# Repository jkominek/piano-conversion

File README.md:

# About

This represents work on hardware/software for converting acoustic
pianos in to full featured MIDI controllers. The idea is to take
untunable pianos, or pianos whose restoration cost would wildly
exceed their value, and make something useful out of them.

See [the FAQ](https://github.com/jkominek/piano-conversion/wiki/FAQ)
to have common / likely questions answered.

Later work may expand that scope.

It was inspired by Evgeni Kumanov (CyberGene)'s "Cybrid" controller:
https://github.com/ekumanov/cybrid/

# Warning!

The hardware designs are unfinished. Some have not been fabricated.
Most have barely been tested, and there is not firmware to run a
completed system.

See the [Status page](https://github.com/jkominek/piano-conversion/wiki/Status) for where things stand.

# A Very Brief Overview

* hardware
  * Where most of the work has taken place. KiCad schematics and board
    layouts for the system.
* cubemx
  * STCubeMX files which correspond to the boards, the idea being that
    if you want to write your own firmware, you can start from here,
    and know that your pin assignments and such are all sane.
* firmware
  * Board firmware, some other stuff
* analyses
  * Data collected, and code/notes for processing it.
* mechanical
  * OpenSCAD files for physical parts which have been useful in
    construction of my prototype.

# More

See [DESIGN.md](https://github.com/jkominek/piano-conversion/blob/master/DESIGN.md) for system design information.

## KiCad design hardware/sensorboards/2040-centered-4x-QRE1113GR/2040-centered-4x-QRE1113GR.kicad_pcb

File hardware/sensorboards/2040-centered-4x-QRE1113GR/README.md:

These are the KiCad files for a sensorboard containing 4 QRE1113GR (surface mount) as in the raytracing below

The image depicts an assembly of sensorboards on thick and thin rails (in dark gray, on the top).
The thick rails will be used for hammer sensors. The hammers will come from down in this picture
and the keys are "inside the screen" toward the left.

The lighter grey "sensor protector" will absorb at least part of the hammer impacts.
All the hammer boards will have those installed, but it is not shown on the board
to the right to show better the board itself. There is a levitating "sensor protector"
on the left, showing the other side with the clearance for the pins.

The board on the left, on the thinner extrusion is identical to the others. The assembly
is slightly different in that the jumper connector will be mounted on
the other side of the board. That, and the thinner extrusion make it a "key sensor" board.
It will need to be flipped upside down for the purpose, and lowered under the keys which
are not shown in this image. All keys will have them (also the keys not damped on a piano:
note off is still needed for MIDI even if it might be ignored by the virtual instrument for
the highest notes of the piano).

Note also that the 3D model of the sensor is taken from a different one and not very accurate
neither quantitatively (i.e. dimensions are incorrect) nor qualitatively (for example it does
not show the little "dips" where the LED and the phototransistors are).
The subdirectory rendering contains more information on the 3D render process

If you want to avoid the hassle of ordering, I am trying to make the whole process easier for you,
but it is not fully working yet. You can track that progress
[here](https://www.pcbway.com/project/shareproject/W341931AX1N3_gerber_54f46d6c.html)

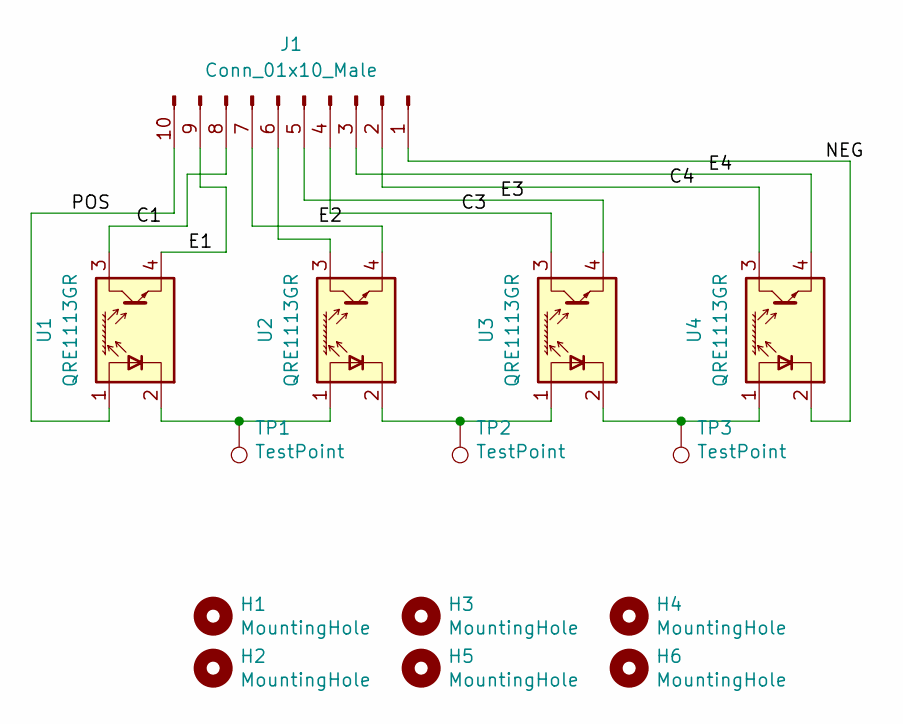
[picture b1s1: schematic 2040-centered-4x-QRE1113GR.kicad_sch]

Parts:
H1, H2, H3, H4, H5, H6: MountingHole; MountingHole_3.2mm_M3
J1: Conn_01x10_Male; PinHeader_1x10_P2.54mm_Vertical
TP1, TP2, TP3: TestPoint; TestPoint_Pad_1.0x1.0mm
U1, U2, U3, U4: QRE1113GR; MPN QRE1113GR

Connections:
/C1: J1.8, U1.3
/C3: J1.4, U3.3
/C4: J1.2, U4.3
/E1: J1.9, U1.4
/E2: J1.7, U2.4
/E3: J1.5, U3.4
/E4: J1.3, U4.4
/NEG: J1.1, U4.2 (K)
/POS: J1.10, U1.1 (A)
unnamed: TP1.1, U1.2 (K), U2.1 (A)
unnamed: TP2.1, U2.2 (K), U3.1 (A)
unnamed: TP3.1, U3.2 (K), U4.1 (A)
unnamed: J1.6, U2.3

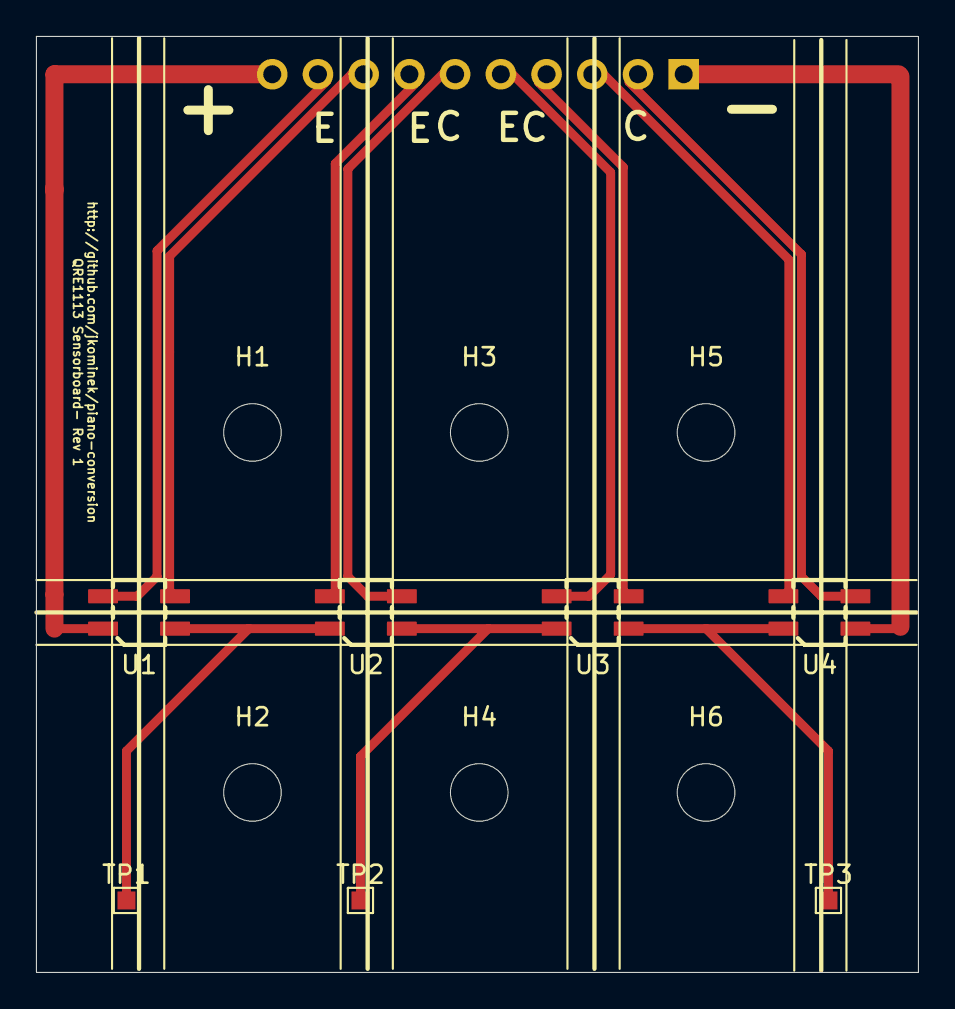
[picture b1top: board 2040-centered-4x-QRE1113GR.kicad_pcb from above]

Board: 2 copper layers, 49.0 x 52.0 mm, 14 parts (1 on the bottom side), 13 nets.

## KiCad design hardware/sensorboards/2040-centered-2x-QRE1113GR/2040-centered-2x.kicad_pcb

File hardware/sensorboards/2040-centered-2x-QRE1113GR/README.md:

These are the KiCad files for a sensoroard containing 2 QRE1113GR (surface mount) as below

The board is asymmetric. I have done that to allow a stable mounting even if the board should be attached to the extrusion via
spacers (which are necessary if one does not fix in other ways the difference between the bass hammers and the rest -- due to the fact
that bass strings cross the other ones and hence are at a different height).

As it should be clear from the picture, this means that 2x sensorboards can **NOT** be used for the whole piano. In fact, a sensor of one side
is too distant from the side of the board to be able to fit another sensorboard nearby and still match the subsequent hammer.
These boards have been designed to be used **only** as end options for the last one or two hammers in each section, where a 4x sensorboard
would not be desirable (for example for space reasons).

At first it seems that this sensorboard can be used only on one side of the section, however if one is flexible with the connector placement
(front or back of the rail) this is not actually a limitation: a 180 degree rotation over the vertical axis will allow to this sensorboard
to be either the first or the last of each section.

Notes:

1. The 3D model of the sensor is taken from a different one and not very accurate (for example it does not show the little "dips" where
   the LED and the phototransistors are)
2. I am not sure I am allowed to include the CAD model of the aluminum extrusion, but you can download it yourself from
   [the HFS4040 page](https://us.misumi-ec.com/vona2/detail/110302684530/) on the Misumi website, and associate it to that "hole" out
   of the board

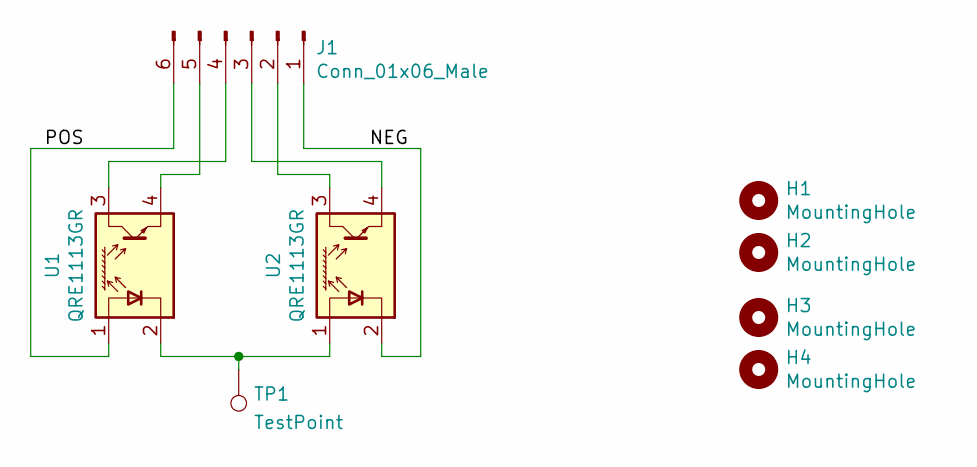
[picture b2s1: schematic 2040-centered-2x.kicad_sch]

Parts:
H1, H2, H3, H4: MountingHole; MountingHole_3.2mm_M3
J1: Conn_01x06_Male; Pin_Header_Angled_1x06_Pitch2.54mm
TP1: TestPoint; TestPoint_Pad_1.0x1.0mm
U1, U2: QRE1113GR

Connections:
/NEG: J1.1, U2.2 (K)
/POS: J1.6, U1.1 (A)
unnamed: TP1.1, U1.2 (K), U2.1 (A)
unnamed: J1.4, U1.3 (C)
unnamed: J1.5, U1.4 (E)
unnamed: J1.2, U2.3 (C)
unnamed: J1.3, U2.4 (E)

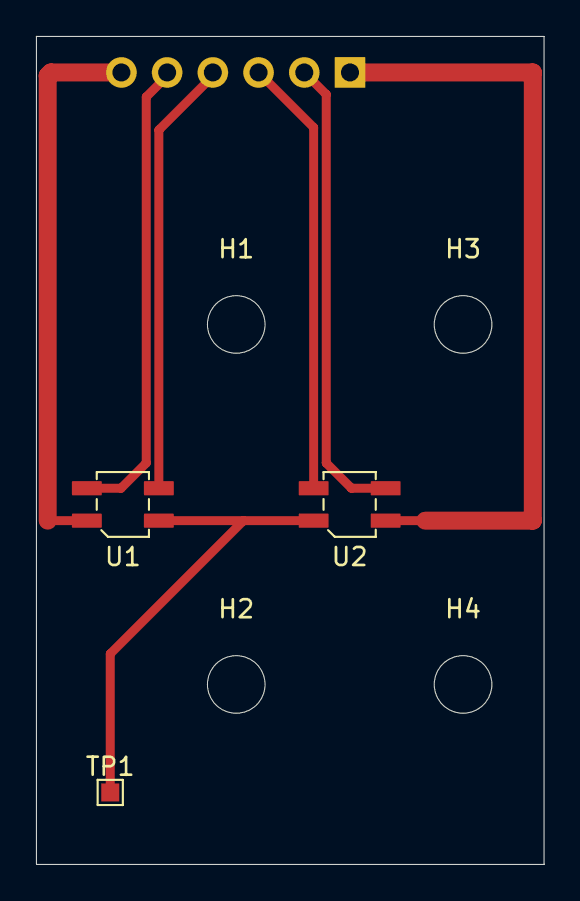
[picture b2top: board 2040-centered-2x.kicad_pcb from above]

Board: 2 copper layers, 28.2 x 46.0 mm, 8 parts (1 on the bottom side), 7 nets.

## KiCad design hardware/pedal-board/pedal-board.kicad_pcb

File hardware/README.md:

# What's in here

* adc-board
  * An STM32H743 reading 22 ADC channels and sending the results over RS485.
* led-power
  * Provides power to 8 strings of 22 CNY70 IR LEDs. Needs +48V. Optional I2C control.
* led-test-bar
  * For development only: little bar that holds a bunch of LEDs for testing the LED power board.
* link-adapter
  * For development only: allows a PC to connect to an ADC or main board.
* main-board
  * 8 ADC boards can plug in, their processed signals are managed
    by another STM32H743 and converted to MIDI in its various forms.
    Intended mainly for USB use, also has ethernet designed in.
    For all of the optional accessories, there are three I2C ports in
    the form of Qwiic connectors, for plugging in MIDI & pedal boards,
    and whatever other craziness you can conjure up.
* midi-board
  * An I2C to MIDI DIN board. Gets the extra UART, optos and DIN
    connectors off the main board so they're not taking up space if
    you don't need them.
* pedal-board
  * 4 1/4" TRS jacks for common MIDI keyboard pedals. STM32G0 for reading
    the signals and making them available to the main board via I2C.
* sensorboard-tester
  * For development/manufacture only, for testing/measuring sensorboards/CNY70s.
* sensorboards
  * Directory with a variety of board configurations for holding CNY70 sensors.

To put a sensor on every hammer and key of an 88 key piano, you would need:

* 176 sensor boards
* 8 ADC boards
* 1 main board
* 1 LED power board

Everything else is optional, but might make your life better.

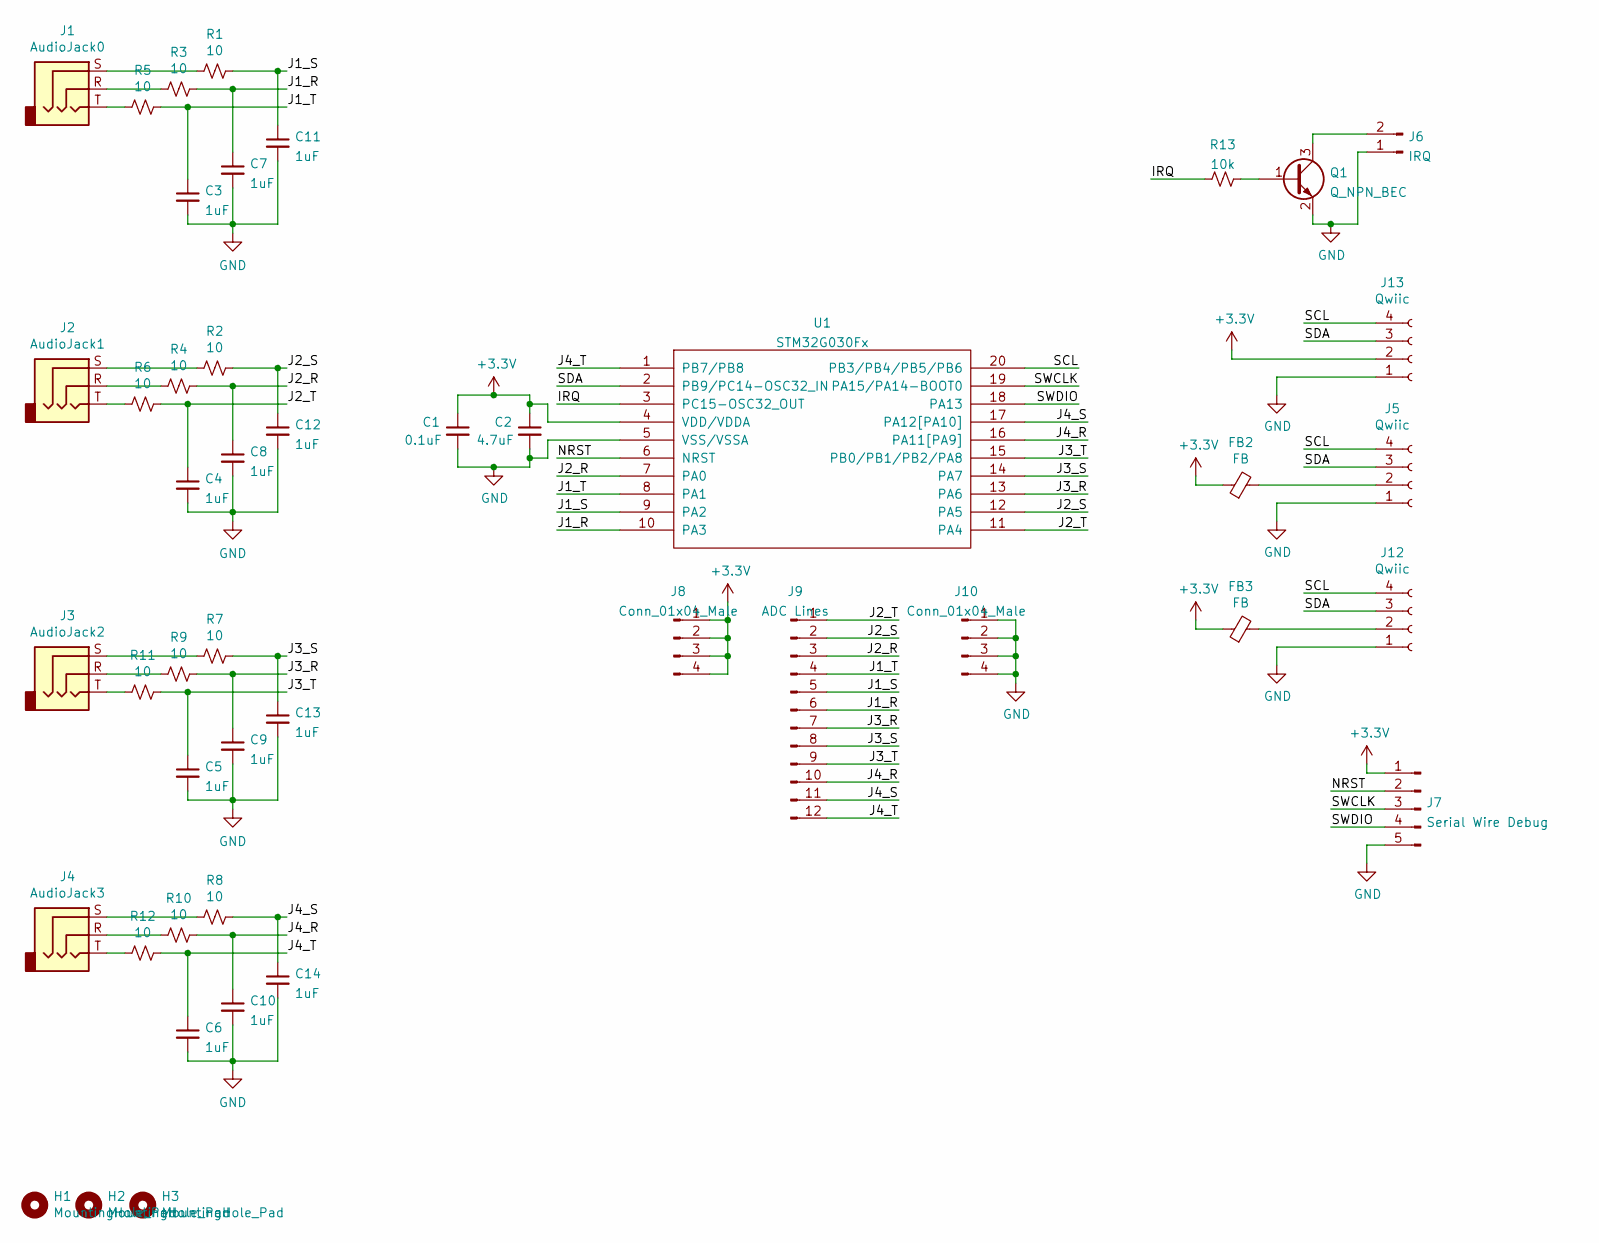
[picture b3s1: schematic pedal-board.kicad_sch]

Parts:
C1: 0.1uF; C_0805_2012Metric_Pad1.18x1.45mm_HandSolder
C2: 4.7uF; C_0805_2012Metric_Pad1.18x1.45mm_HandSolder
C3, C4, C5, C6, C7, C8, C9, C10, C11, C12, C13, C14: 1uF; C_0805_2012Metric_Pad1.18x1.45mm_HandSolder
FB2, FB3: FB; L_0805_2012Metric_Pad1.05x1.20mm_HandSolder
H1, H2, H3: MountingHole_Pad; MountingHole_3.2mm_M3
J1: AudioJack0; SJ-63053A
J2: AudioJack1; SJ-63053A
J3: AudioJack2; SJ-63053A
J4: AudioJack3; SJ-63053A
J5, J12: Qwiic; JST_SH_SM04B-SRSS-TB_04x1.00mm_Angled
J6: IRQ; PinHeader_1x02_P2.54mm_Vertical
J7: Serial Wire Debug; PinHeader_1x05_P2.54mm_Vertical
J8, J10: Conn_01x04_Male; PinHeader_1x04_P2.54mm_Vertical
J9: ADC Lines; PinHeader_1x12_P2.54mm_Vertical
J13: Qwiic; PinHeader_1x04_P2.54mm_Vertical
Q1: Q_NPN_BEC; SOT-23
R1, R2, R3, R4, R5, R6, R7, R8, R9, R10, R11, R12: 10; R_0805_2012Metric_Pad1.20x1.40mm_HandSolder
R13: 10k; R_0805_2012Metric_Pad1.20x1.40mm_HandSolder
U1: STM32G030Fx; TSSOP-20_4.4x6.5mm_P0.65mm

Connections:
+3V3: C1.1, C2.1, FB2.1, FB3.1, J7.1, J8.1, J8.2, J8.3, J8.4, J13.2, U1.4 (VDD/VDDA)
/IRQ: R13.1, U1.3 (PC15-OSC32_OUT)
/J1_R: C7.1, J9.6, R3.1, U1.10 (PA3)
/J1_S: C11.1, J9.5, R1.1, U1.9 (PA2)
/J1_T: C3.1, J9.4, R5.1, U1.8 (PA1)
/J2_R: C8.1, J9.3, R4.1, U1.7 (PA0)
/J2_S: C12.1, J9.2, R2.1, U1.12 (PA5)
/J2_T: C4.1, J9.1, R6.1, U1.11 (PA4)
/J3_R: C9.1, J9.7, R9.1, U1.13 (PA6)
/J3_S: C13.1, J9.8, R7.1, U1.14 (PA7)
/J3_T: C5.1, J9.9, R11.1, U1.15 (PB0/PB1/PB2/PA8)
/J4_R: C10.1, J9.10, R10.1, U1.16 (PA11[PA9])
/J4_S: C14.1, J9.11, R8.1, U1.17 (PA12[PA10])
/J4_T: C6.1, J9.12, R12.1, U1.1 (PB7/PB8)
/NRST: J7.2, U1.6 (NRST)
/SCL: J5.4, J12.4, J13.4, U1.20 (PB3/PB4/PB5/PB6)
/SDA: J5.3, J12.3, J13.3, U1.2 (PB9/PC14-OSC32_IN)
/SWCLK: J7.3, U1.19 (PA15/PA14-BOOT0)
/SWDIO: J7.4, U1.18 (PA13)
GND: C1.2, C2.2, C3.2, C4.2, C5.2, C6.2, C7.2, C8.2, C9.2, C10.2, C11.2, C12.2, C13.2, C14.2, J5.1, J6.1, J7.5, J10.1, J10.2, J10.3, J10.4, J12.1, J13.1, Q1.2 (E), U1.5 (VSS/VSSA)
unnamed: FB2.2, J5.2
unnamed: FB3.2, J12.2
unnamed: J1.R, R3.2
unnamed: J1.S, R1.2
unnamed: J1.T, R5.2
unnamed: J2.R, R4.2
unnamed: J2.S, R2.2
unnamed: J2.T, R6.2
unnamed: J3.R, R9.2
unnamed: J3.S, R7.2
unnamed: J3.T, R11.2
unnamed: J4.R, R10.2
unnamed: J4.S, R8.2
unnamed: J4.T, R12.2
unnamed: J6.2, Q1.3 (C)
unnamed: Q1.1 (B), R13.2

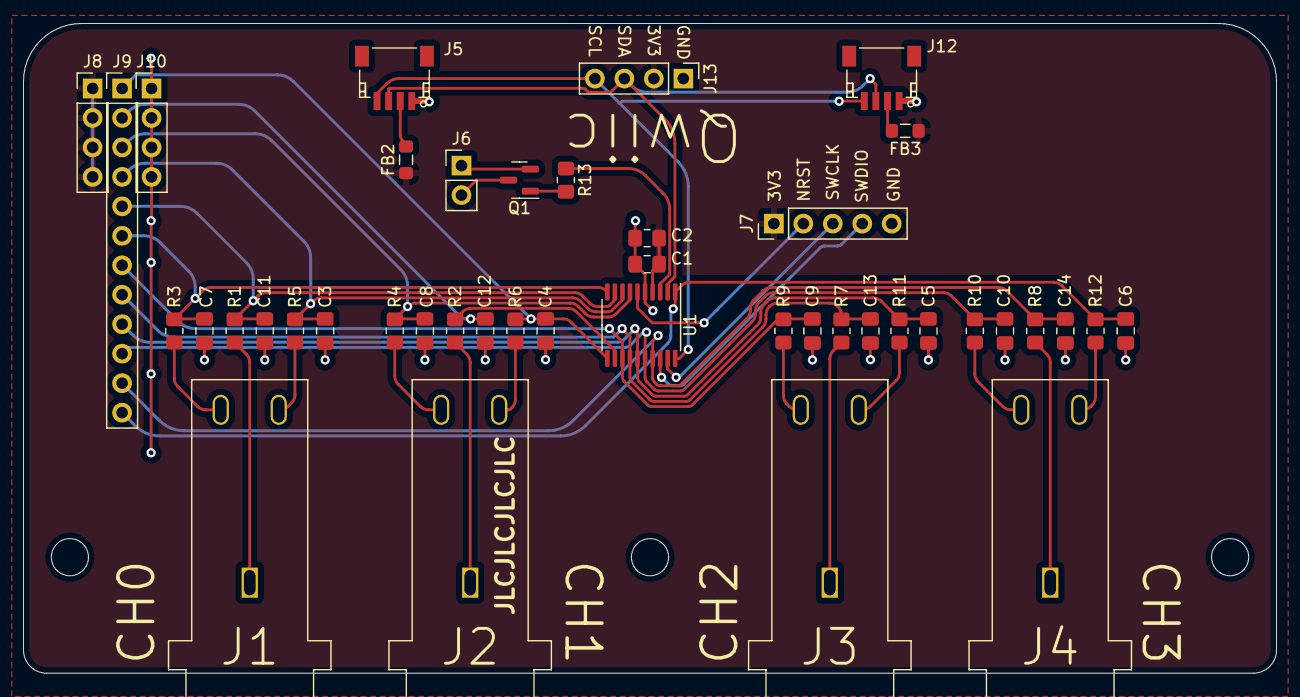
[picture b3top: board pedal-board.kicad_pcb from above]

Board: 2 copper layers, 108.0 x 56.0 mm, 46 parts (0 on the bottom side), 36 nets.

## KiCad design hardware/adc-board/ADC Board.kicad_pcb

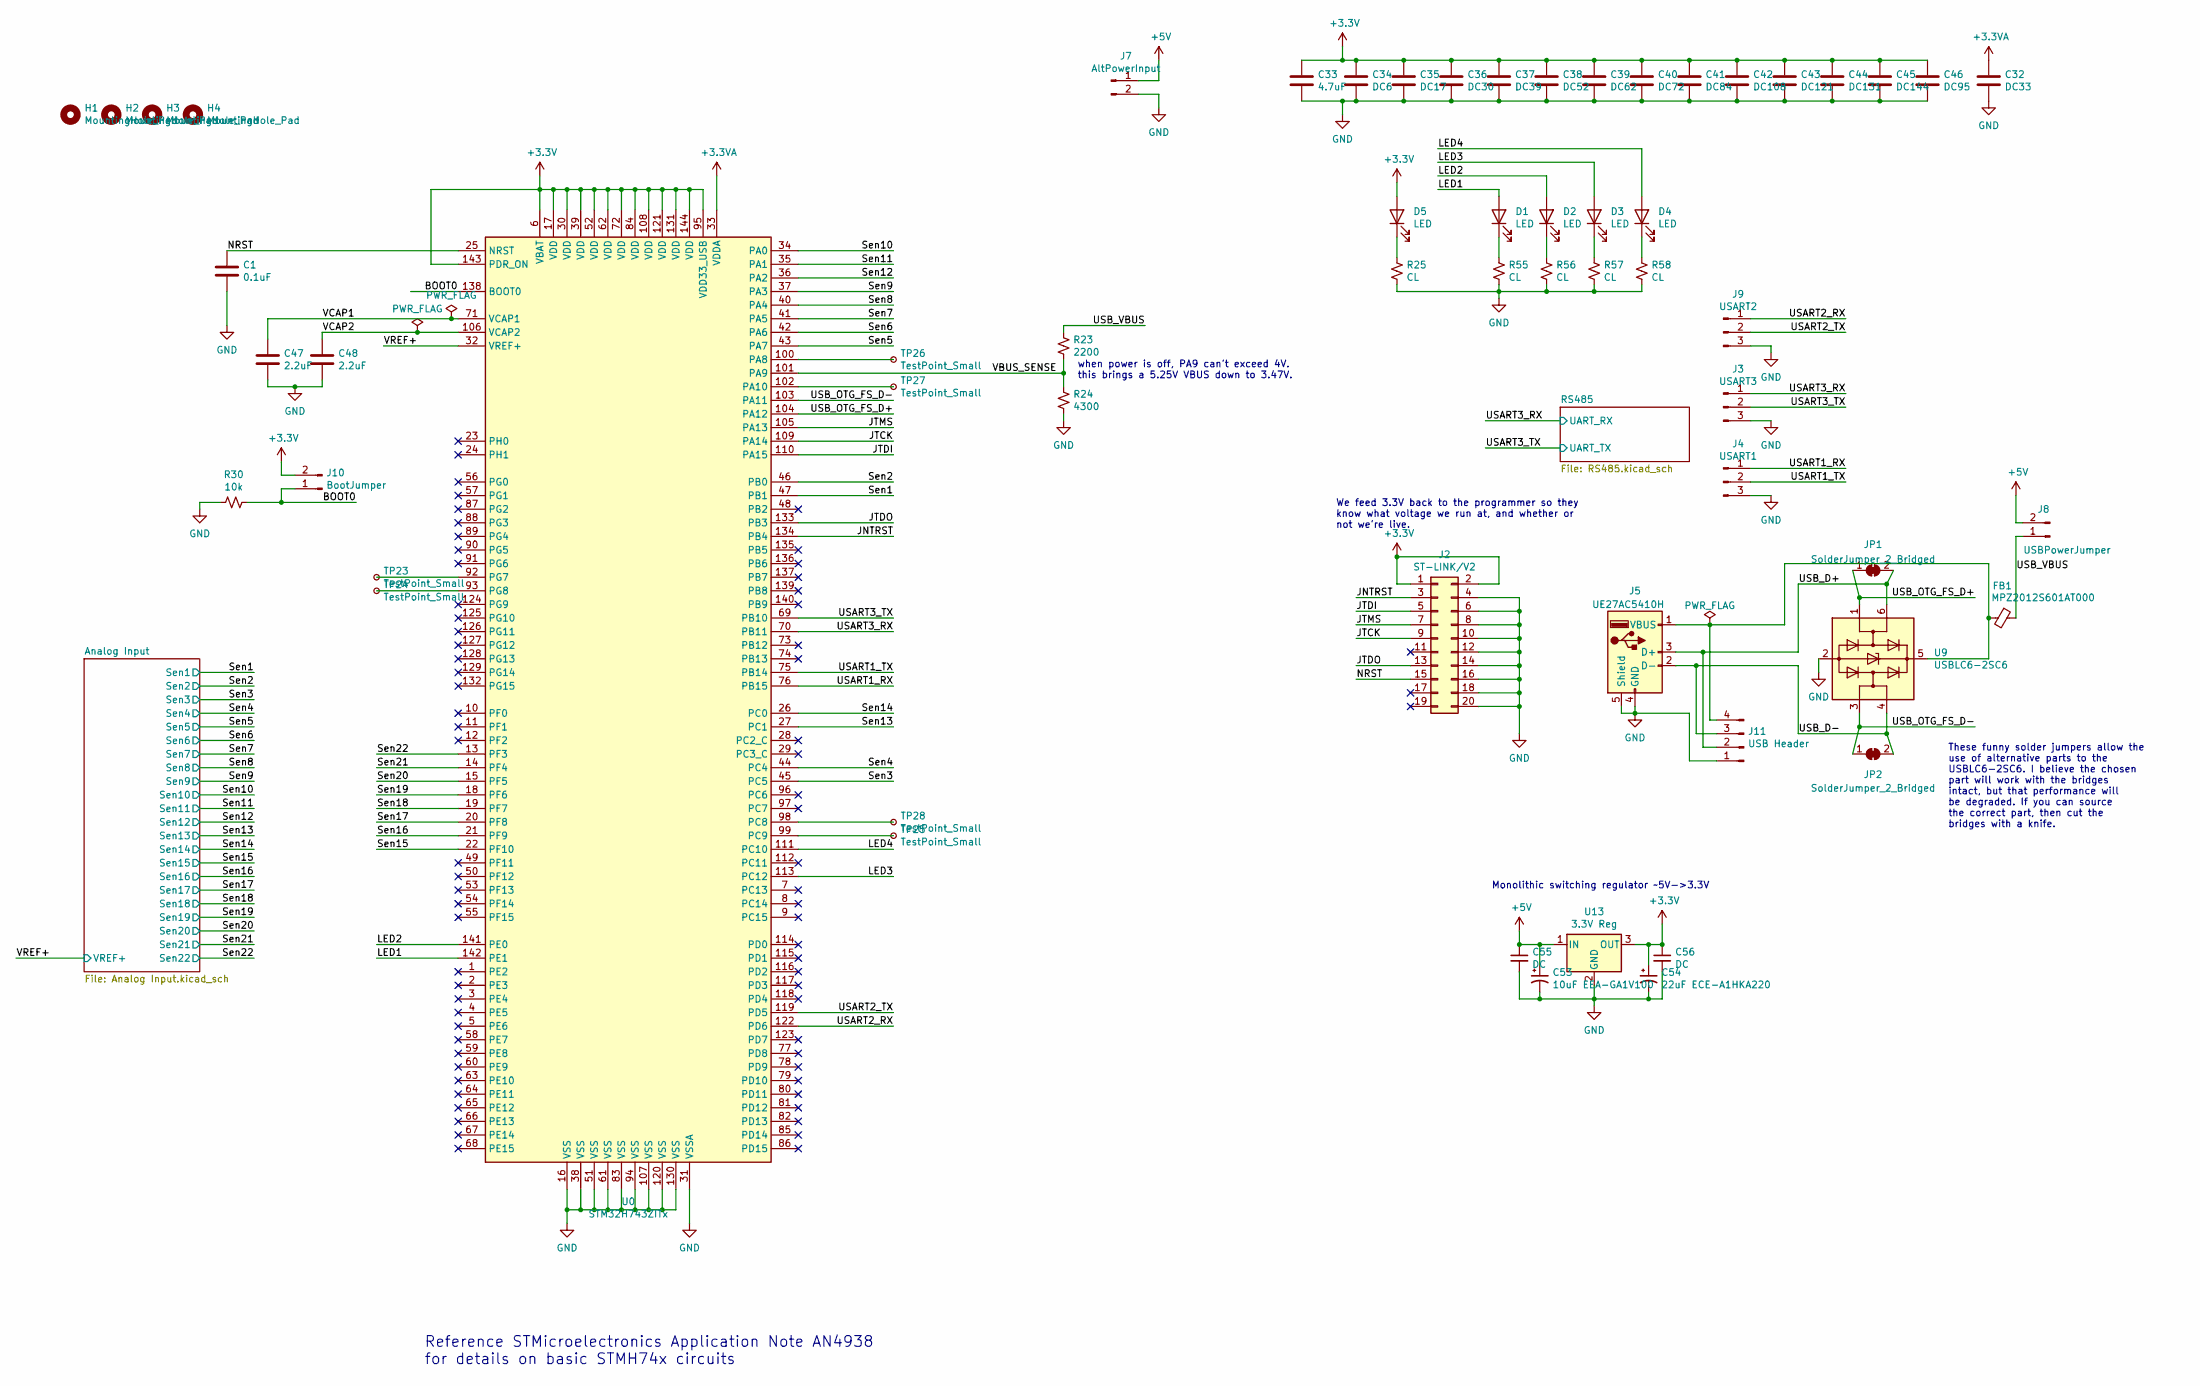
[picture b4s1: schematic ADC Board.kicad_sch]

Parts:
C1: 0.1uF; C_0805_2012Metric
C32: DC33; C_0805_2012Metric
C33: 4.7uF; C_0805_2012Metric
C34: DC6; C_0805_2012Metric
C35: DC17; C_0805_2012Metric
C36: DC30; C_0805_2012Metric
C37: DC39; C_0805_2012Metric
C38: DC52; C_0805_2012Metric
C39: DC62; C_0805_2012Metric
C40: DC72; C_0805_2012Metric
C41: DC84; C_0805_2012Metric
C42: DC108; C_0805_2012Metric
C43: DC121; C_0805_2012Metric
C44: DC131; C_0805_2012Metric
C45: DC144; C_0805_2012Metric
C46: DC95; C_0805_2012Metric
C47, C48: 2.2uF; C_0805_2012Metric
C53: 10uF EEA-GA1V100; CP_Elec_5x5.3
C54: 22uF ECE-A1HKA220; CP_Elec_6.3x5.3
C55, C56: DC; C_0805_2012Metric
D1, D2, D3, D4, D5: LED; LED_0805_2012Metric_Pad1.15x1.40mm_HandSolder
FB1: MPZ2012S601AT000; L_0805_2012Metric_Pad1.05x1.20mm_HandSolder
H1, H2, H3, H4: MountingHole_Pad; MountingHole_3.2mm_M3
J2: ST-LINK/V2; Pin_Header_Straight_2x10_Pitch2.54mm
J3: USART3; Pin_Header_Straight_1x03_Pitch2.54mm
J4: USART1; Pin_Header_Straight_1x03_Pitch2.54mm
J5: UE27AC5410H; USB_A_Molex_67643_Horizontal
J7: AltPowerInput; Pin_Header_Straight_1x02_Pitch2.54mm
J8: USBPowerJumper; Pin_Header_Straight_1x02_Pitch2.54mm
J9: USART2; Pin_Header_Straight_1x03_Pitch2.54mm
J10: BootJumper; Pin_Header_Straight_1x02_Pitch2.54mm
J11: USB Header; Pin_Header_Straight_1x04_Pitch2.54mm
JP1, JP2: SolderJumper_2_Bridged; SolderJumper-2_P1.3mm_Bridged_RoundedPad1.0x1.5mm
R23: 2200; R_0805_2012Metric
R24: 4300; R_0805_2012Metric
R25, R55, R56, R57, R58: CL; R_0805_2012Metric
R30: 10k; R_0805_2012Metric
TP23, TP24, TP25, TP26, TP27, TP28: TestPoint_Small; TestPoint_Pad_D1.5mm
U0: STM32H743ZITx; TQFP-144_20x20mm_P0.5mm
U9: USBLC6-2SC6; SOT-23-6_Handsoldering
U13: 3.3V Reg; TO-220-3_Vertical

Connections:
+3.3VA: C32.1, U0.33 (VDDA); also elsewhere on the board
+3V3: C33.1, C34.1, C35.1, C36.1, C37.1, C38.1, C39.1, C40.1, C41.1, C42.1, C43.1, C44.1, C45.1, C46.1, C54.1, C56.1, D5.2 (A), J2.1, J2.2, J10.2, U0.6 (VBAT), U0.17 (VDD), U0.30 (VDD), U0.39 (VDD), U0.52 (VDD), U0.62 (VDD), U0.72 (VDD), U0.84 (VDD), U0.95 (VDD33_USB), U0.108 (VDD), U0.121 (VDD), U0.131 (VDD), U0.143 (PDR_ON), U0.144 (VDD), U13.3 (OUT); also elsewhere on the board
+5V: C53.1, C55.1, J7.1, J8.2, U13.1 (IN); also elsewhere on the board
/BOOT0: J10.1, R30.1, U0.138 (BOOT0)
/JNTRST: J2.3, U0.134 (PB4)
/JTCK: J2.9, U0.109 (PA14)
/JTDI: J2.5, U0.110 (PA15)
/JTDO: J2.13, U0.133 (PB3)
/JTMS: J2.7, U0.105 (PA13)
/LED1: D1.2 (A), U0.142 (PE1)
/LED2: D2.2 (A), U0.141 (PE0)
/LED3: D3.2 (A), U0.113 (PC12)
/LED4: D4.2 (A), U0.111 (PC10)
/NRST: C1.1, J2.15, U0.25 (NRST)
/Sen1: U0.47 (PB1); also elsewhere on the board
/Sen2: U0.46 (PB0); also elsewhere on the board
/Sen3: U0.45 (PC5); also elsewhere on the board
/Sen4: U0.44 (PC4); also elsewhere on the board
/Sen5: U0.43 (PA7); also elsewhere on the board
/Sen6: U0.42 (PA6); also elsewhere on the board
/Sen7: U0.41 (PA5); also elsewhere on the board
/Sen8: U0.40 (PA4); also elsewhere on the board
/Sen9: U0.37 (PA3); also elsewhere on the board
/Sen10: U0.34 (PA0); also elsewhere on the board
/Sen11: U0.35 (PA1); also elsewhere on the board
/Sen12: U0.36 (PA2); also elsewhere on the board
/Sen13: U0.27 (PC1); also elsewhere on the board
/Sen14: U0.26 (PC0); also elsewhere on the board
/Sen15: U0.22 (PF10); also elsewhere on the board
/Sen16: U0.21 (PF9); also elsewhere on the board
/Sen17: U0.20 (PF8); also elsewhere on the board
/Sen18: U0.19 (PF7); also elsewhere on the board
/Sen19: U0.18 (PF6); also elsewhere on the board
/Sen20: U0.15 (PF5); also elsewhere on the board
/Sen21: U0.14 (PF4); also elsewhere on the board
/Sen22: U0.13 (PF3); also elsewhere on the board
/USART1_RX: J4.1, U0.76 (PB15)
/USART1_TX: J4.2, U0.75 (PB14)
/USART2_RX: J9.1, U0.122 (PD6)
/USART2_TX: J9.2, U0.119 (PD5)
/USART3_RX: J3.1, U0.70 (PB11); also elsewhere on the board
/USART3_TX: J3.2, U0.69 (PB10); also elsewhere on the board
/USB_D+: J5.3 (D+), J11.2, JP1.2 (B), U9.6 (I/O1)
/USB_D-: J5.2 (D-), J11.3, JP2.2 (B), U9.4 (I/O2)
/USB_OTG_FS_D+: JP1.1 (A), U0.104 (PA12), U9.1 (I/O1)
/USB_OTG_FS_D-: JP2.1 (A), U0.103 (PA11), U9.3 (I/O2)
/USB_VBUS: FB1.1, J8.1, R23.1
/VBUS_SENSE: R23.2, R24.1, U0.101 (PA9)
/VCAP1: C47.1, U0.71 (VCAP1)
/VCAP2: C48.1, U0.106 (VCAP2)
/VREF+: U0.32 (VREF+); also elsewhere on the board
GND: C1.2, C32.2, C33.2, C34.2, C35.2, C36.2, C37.2, C38.2, C39.2, C40.2, C41.2, C42.2, C43.2, C44.2, C45.2, C46.2, C47.2, C48.2, C53.2, C54.2, C55.2, C56.2, J2.4, J2.6, J2.8, J2.10, J2.12, J2.14, J2.16, J2.18, J2.20, J3.3, J4.3, J5.4 (GND), J5.5 (Shield), J7.2, J9.3, J11.1, R24.2, R25.2, R30.2, R55.2, R56.2, R57.2, R58.2, U0.16 (VSS), U0.31 (VSSA), U0.38 (VSS), U0.51 (VSS), U0.61 (VSS), U0.83 (VSS), U0.94 (VSS), U0.107 (VSS), U0.120 (VSS), U0.130 (VSS), U9.2 (GND), U13.2 (GND); also elsewhere on the board
unnamed: D1.1 (K), R55.1
unnamed: D2.1 (K), R56.1
unnamed: D3.1 (K), R57.1
unnamed: D4.1 (K), R58.1
unnamed: D5.1 (K), R25.1
unnamed: FB1.2, J5.1 (VBUS), J11.4, U9.5 (VBUS)
unnamed: TP23.1, U0.92 (PG7)
unnamed: TP24.1, U0.93 (PG8)
unnamed: TP25.1, U0.99 (PC9)
unnamed: TP26.1, U0.100 (PA8)
unnamed: TP27.1, U0.102 (PA10)
unnamed: TP28.1, U0.98 (PC8)

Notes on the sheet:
Monolithic switching regulator ~5V->3.3V
We feed 3.3V back to the programmer so they know what voltage we run at, and whether or not we're live.
Reference STMicroelectronics Application Note AN4938 for details on basic STMH74x circuits
These funny solder jumpers allow the use of alternative parts to the USBLC6-2SC6. I believe the chosen part will work with the bridges intact, but that performance will be degraded. If you can source the correct part, then cut the bridges with a knife.
when power is off, PA9 can't exceed 4V. this brings a 5.25V VBUS down to 3.47V.

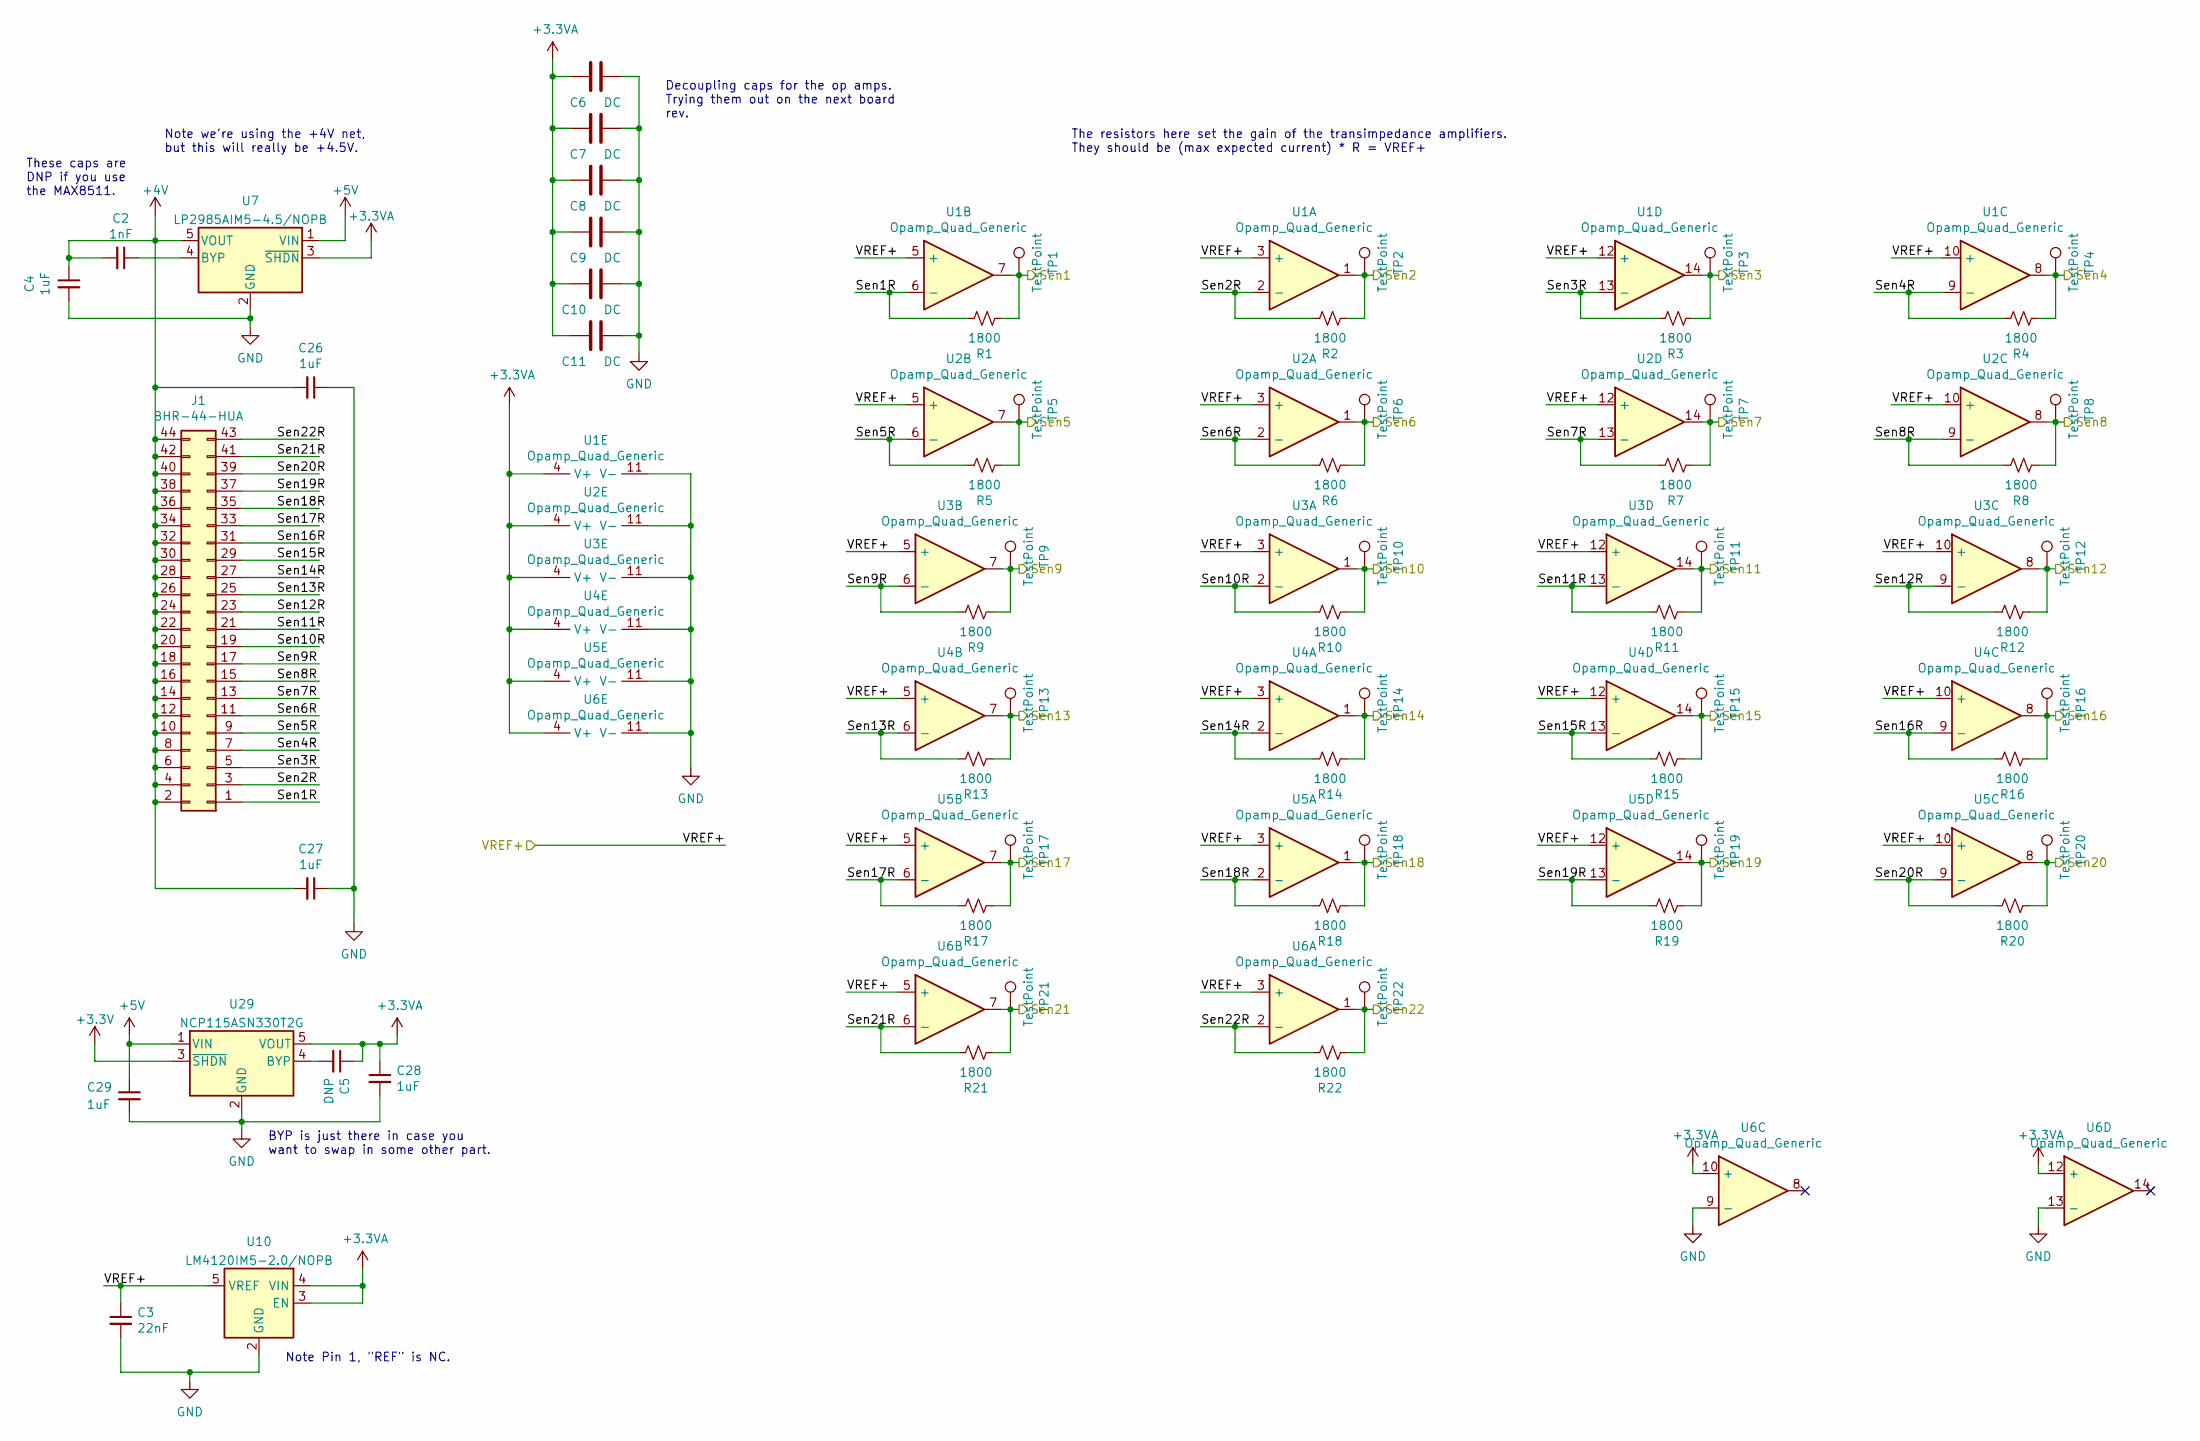
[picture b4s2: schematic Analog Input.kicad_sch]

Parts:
C2: 1nF; C_0805_2012Metric
C3: 22nF; C_0805_2012Metric
C4, C26, C27, C28, C29: 1uF; C_0805_2012Metric
C5: DNP; C_0805_2012Metric
C6, C7, C8, C9, C10, C11: DC; C_0805_2012Metric
J1: BHR-44-HUA; Pin_Header_Angled_2x22_Pitch2.54mm
R1, R2, R3, R4, R5, R6, R7, R8, R9, R10, R11, R12, R13, R14, R15, R16, R17, R18, R19, R20, R21, R22: 1800; R_0805_2012Metric
TP1, TP2, TP3, TP4, TP5, TP6, TP7, TP8, TP9, TP10, TP11, TP12, TP13, TP14, TP15, TP16, TP17, TP18, TP19, TP20, TP21, TP22: TestPoint; TestPoint_Pad_D1.0mm
U1, U2, U3, U4, U5, U6: Opamp_Quad_Generic; TSSOP-14_4.4x5mm_P0.65mm
U7: LP2985AIM5-4.5/NOPB; SOT-23-5
U10: LM4120IM5-2.0/NOPB; SOT-23-5
U29: NCP115ASN330T2G; SOT-23-5

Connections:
+3.3VA: C5.1, C6.1, C7.1, C8.1, C9.1, C10.1, C11.1, C28.1, U1.4 (V+), U2.4 (V+), U3.4 (V+), U4.4 (V+), U5.4 (V+), U6.4 (V+), U6.10 (+), U6.12 (+), U7.3 (~SHDN), U10.3 (EN), U10.4 (VIN), U29.5 (VOUT); also elsewhere on the board
+3V3: U29.3 (~SHDN); also elsewhere on the board
+4V: C2.2, C4.1, C26.2, C27.2, J1.2, J1.4, J1.6, J1.8, J1.10, J1.12, J1.14, J1.16, J1.18, J1.20, J1.22, J1.24, J1.26, J1.28, J1.30, J1.32, J1.34, J1.36, J1.38, J1.40, J1.42, J1.44, U7.5 (VOUT)
+5V: C29.1, U7.1 (VIN), U29.1 (VIN); also elsewhere on the board
/Analog Input/Sen1R: J1.1, R1.1, U1.6 (-)
/Analog Input/Sen2R: J1.3, R2.1, U1.2 (-)
/Analog Input/Sen3R: J1.5, R3.1, U1.13 (-)
/Analog Input/Sen4R: J1.7, R4.1, U1.9 (-)
/Analog Input/Sen5R: J1.9, R5.1, U2.6 (-)
/Analog Input/Sen6R: J1.11, R6.1, U2.2 (-)
/Analog Input/Sen7R: J1.13, R7.1, U2.13 (-)
/Analog Input/Sen8R: J1.15, R8.1, U2.9 (-)
/Analog Input/Sen9R: J1.17, R9.1, U3.6 (-)
/Analog Input/Sen10R: J1.19, R10.1, U3.2 (-)
/Analog Input/Sen11R: J1.21, R11.1, U3.13 (-)
/Analog Input/Sen12R: J1.23, R12.1, U3.9 (-)
/Analog Input/Sen13R: J1.25, R13.1, U4.6 (-)
/Analog Input/Sen14R: J1.27, R14.1, U4.2 (-)
/Analog Input/Sen15R: J1.29, R15.1, U4.13 (-)
/Analog Input/Sen16R: J1.31, R16.1, U4.9 (-)
/Analog Input/Sen17R: J1.33, R17.1, U5.6 (-)
/Analog Input/Sen18R: J1.35, R18.1, U5.2 (-)
/Analog Input/Sen19R: J1.37, R19.1, U5.13 (-)
/Analog Input/Sen20R: J1.39, R20.1, U5.9 (-)
/Analog Input/Sen21R: J1.41, R21.1, U6.6 (-)
/Analog Input/Sen22R: J1.43, R22.1, U6.2 (-)
/Sen1: R1.2, TP1.1, U1.7; also elsewhere on the board
/Sen2: R2.2, TP2.1, U1.1; also elsewhere on the board
/Sen3: R3.2, TP3.1, U1.14; also elsewhere on the board
/Sen4: R4.2, TP4.1, U1.8; also elsewhere on the board
/Sen5: R5.2, TP5.1, U2.7; also elsewhere on the board
/Sen6: R6.2, TP6.1, U2.1; also elsewhere on the board
/Sen7: R7.2, TP7.1, U2.14; also elsewhere on the board
/Sen8: R8.2, TP8.1, U2.8; also elsewhere on the board
/Sen9: R9.2, TP9.1, U3.7; also elsewhere on the board
/Sen10: R10.2, TP10.1, U3.1; also elsewhere on the board
/Sen11: R11.2, TP11.1, U3.14; also elsewhere on the board
/Sen12: R12.2, TP12.1, U3.8; also elsewhere on the board
/Sen13: R13.2, TP13.1, U4.7; also elsewhere on the board
/Sen14: R14.2, TP14.1, U4.1; also elsewhere on the board
/Sen15: R15.2, TP15.1, U4.14; also elsewhere on the board
/Sen16: R16.2, TP16.1, U4.8; also elsewhere on the board
/Sen17: R17.2, TP17.1, U5.7; also elsewhere on the board
/Sen18: R18.2, TP18.1, U5.1; also elsewhere on the board
/Sen19: R19.2, TP19.1, U5.14; also elsewhere on the board
/Sen20: R20.2, TP20.1, U5.8; also elsewhere on the board
/Sen21: R21.2, TP21.1, U6.7; also elsewhere on the board
/Sen22: R22.2, TP22.1, U6.1; also elsewhere on the board
/VREF+: C3.1, U1.3 (+), U1.5 (+), U1.10 (+), U1.12 (+), U2.3 (+), U2.5 (+), U2.10 (+), U2.12 (+), U3.3 (+), U3.5 (+), U3.10 (+), U3.12 (+), U4.3 (+), U4.5 (+), U4.10 (+), U4.12 (+), U5.3 (+), U5.5 (+), U5.10 (+), U5.12 (+), U6.3 (+), U6.5 (+), U10.5 (VREF); also elsewhere on the board
GND: C3.2, C4.2, C6.2, C7.2, C8.2, C9.2, C10.2, C11.2, C26.1, C27.1, C28.2, C29.2, U1.11 (V-), U2.11 (V-), U3.11 (V-), U4.11 (V-), U5.11 (V-), U6.9 (-), U6.11 (V-), U6.13 (-), U7.2 (GND), U10.2 (GND), U29.2 (GND); also elsewhere on the board
unnamed: C2.1, U7.4 (BYP)
unnamed: C5.2, U29.4 (BYP)

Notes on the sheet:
The resistors here set the gain of the transimpedance amplifiers. They should be (max expected current) * R =~{} VREF+
Note Pin 1, "REF" is NC.
Note we're using the +4V net, but this will really be +4.5V.
These caps are DNP if you use the MAX8511.
Decoupling caps for the op amps. Trying them out on the next board rev.
BYP is just there in case you want to swap in some other part.

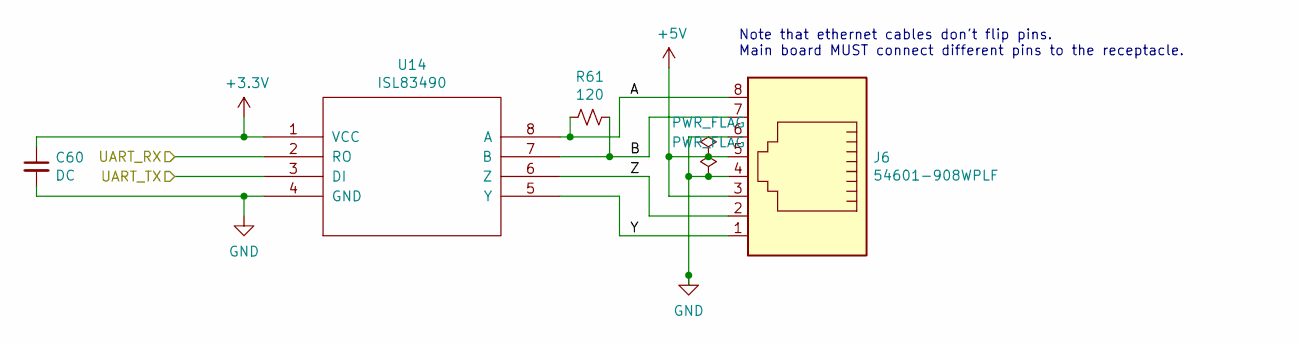
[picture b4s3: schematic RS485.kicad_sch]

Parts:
C60: DC; C_0805_2012Metric
J6: 54601-908WPLF; RJ45_8
R61: 120; R_0805_2012Metric
U14: ISL83490; SOP-8_3.9x4.9mm_P1.27mm

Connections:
+3V3: C60.1, U14.1 (VCC); also elsewhere on the board
+5V: J6.3, J6.5; also elsewhere on the board
/RS485/A: J6.8, R61.2, U14.8 (A)
/RS485/B: J6.7, R61.1, U14.7 (B)
/RS485/Y: J6.1, U14.5 (Y)
/RS485/Z: J6.2, U14.6 (Z)
/USART3_RX: U14.2 (RO); also elsewhere on the board
/USART3_TX: U14.3 (DI); also elsewhere on the board
GND: C60.2, J6.4, J6.6, U14.4 (GND); also elsewhere on the board

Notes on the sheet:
Note that ethernet cables don't flip pins. Main board MUST connect different pins to the receptacle.
